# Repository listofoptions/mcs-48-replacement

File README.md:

# mcs-48-replacement
comaptible pinout controller for the mcs-48 microcontroller line using an AT90USB1286

features:
  - usb esd protection
  - power supply seperation and selection
  - reverse voltage protection (vcc/gnd swap)

  **__DO NOT ATTEMPT TO USE THIS CONTROLLER IN A MCS-48 PROGRAMMER__**
  **__THERE IS NO OVERVOLTAGE PROTECTION ON VDD, PROG, OR EA__**

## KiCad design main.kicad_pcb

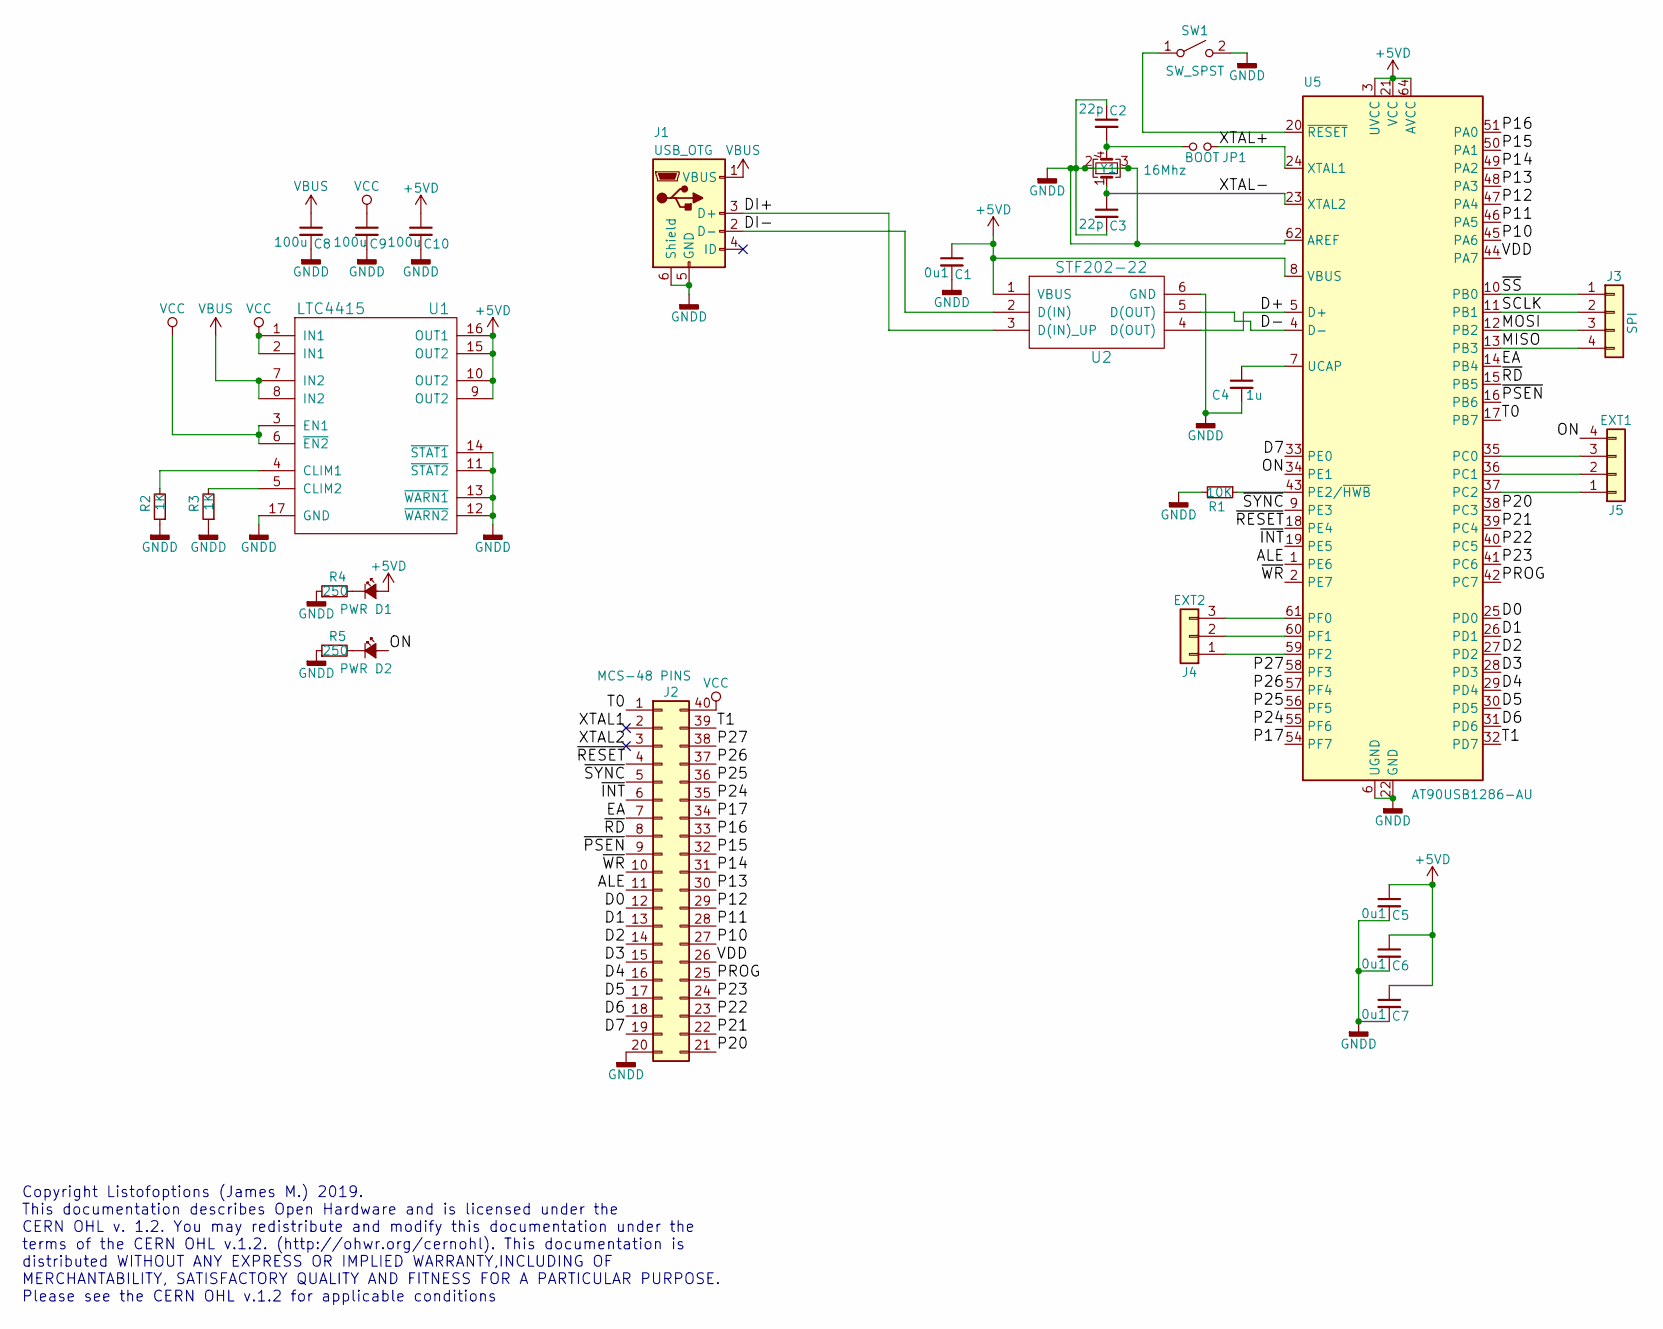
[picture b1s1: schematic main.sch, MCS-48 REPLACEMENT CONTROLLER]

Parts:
C1, C5, C6, C7: 0u1; C_0201
C2, C3: 22p; C_0201
C4: 1u; C_0201
C8, C9, C10: 100u; C_0805
D1, D2: PWR; LED_0402
J1: USB_OTG; USB_Micro-B_Molex-105017-0001
J2: MCS-48 PINS; DIP-40_W15.24mm
J3: SPI; Pin_Header_Straight_1x04_Pitch1.00mm
J4: EXT2; Pin_Header_Straight_1x03_Pitch1.00mm
J5: EXT1; Pin_Header_Straight_1x04_Pitch1.00mm
JP1: BOOT; R_0201_NoSilk
R1: 10K; R_0402
R2, R3: 1K; R_0402
R4, R5: 250; R_0402
SW1: SW_SPST; SW_SPST_B3U-3000P
U1: LTC4415; DFN-16-1EP_3x5mm_Pitch0.5mm
U2: STF202-22; TSOP-6_1.65x3.05mm_Pitch0.95mm
U5: AT90USB1286-AU; QFN-64-1EP_9x9mm_Pitch0.5mm
Y1: 16Mhz; Crystal_SMD_2016-4pin_2.0x1.6mm

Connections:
+5VD: C1.1, C5.1, C6.1, C7.1, C10.1, D1.2 (A), U1.9 (OUT2), U1.10 (OUT2), U1.15 (OUT2), U1.16 (OUT1), U2.1 (VBUS), U5.3 (UVCC), U5.8 (VBUS), U5.21 (VCC), U5.52 (VCC), U5.64 (AVCC)
/ALE: J2.11, U5.1 (PE6)
/D0: J2.12, U5.25 (PD0)
/D1: J2.13, U5.26 (PD1)
/D2: J2.14, U5.27 (PD2)
/D3: J2.15, U5.28 (PD3)
/D4: J2.16, U5.29 (PD4)
/D5: J2.17, U5.30 (PD5)
/D6: J2.18, U5.31 (PD6)
/D7: J2.19, U5.33 (PE0)
/D+: U2.4 (D(OUT)), U5.5 (D+)
/D-: U2.5 (D(OUT)), U5.4 (D-)
/DI+: J1.3 (D+), U2.3 (D(IN)_UP)
/DI-: J1.2 (D-), U2.2 (D(IN))
/EA: J2.7, U5.14 (PB4)
/MISO: J3.4, U5.13 (PB3)
/MOSI: J3.3, U5.12 (PB2)
/ON: D2.2 (A), J5.4, U5.34 (PE1)
/P10: J2.27, U5.45 (PA6)
/P11: J2.28, U5.46 (PA5)
/P12: J2.29, U5.47 (PA4)
/P13: J2.30, U5.48 (PA3)
/P14: J2.31, U5.49 (PA2)
/P15: J2.32, U5.50 (PA1)
/P16: J2.33, U5.51 (PA0)
/P17: J2.34, U5.54 (PF7)
/P20: J2.21, U5.38 (PC3)
/P21: J2.22, U5.39 (PC4)
/P22: J2.23, U5.40 (PC5)
/P23: J2.24, U5.41 (PC6)
/P24: J2.35, U5.55 (PF6)
/P25: J2.36, U5.56 (PF5)
/P26: J2.37, U5.57 (PF4)
/P27: J2.38, U5.58 (PF3)
/PROG: J2.25, U5.42 (PC7)
/SCLK: J3.2, U5.11 (PB1)
/T0: J2.1, U5.17 (PB7)
/T1: J2.39, U5.32 (PD7)
/VDD: J2.26, U5.44 (PA7)
/XTAL+: JP1.2, U5.24 (XTAL1)
/XTAL-: C3.1, U5.23 (XTAL2), Y1.1
/~INT: J2.6, U5.19 (PE5)
/~PSEN: J2.9, U5.16 (PB6)
/~RD: J2.8, U5.15 (PB5)
/~RESET: J2.4, U5.18 (PE4)
/~SS: J3.1, U5.10 (PB0)
/~SYNC: J2.5, U5.9 (PE3)
/~WR: J2.10, U5.2 (PE7)
GNDD: C1.2, C2.1, C3.2, C4.2, C5.2, C6.2, C7.2, C8.2, C9.2, C10.2, J1.5 (GND), J1.6 (Shield), J2.20, R1.2, R2.1, R3.1, R4.1, R5.1, SW1.2 (B), U1.11 (~STAT2), U1.12 (~WARN2), U1.13 (~WARN1), U1.14 (~STAT1), U1.17 (GND), U2.6 (GND), U5.6 (UGND), U5.22 (GND), U5.53 (GND), U5.62 (AREF), U5.63 (GND), U5.65, Y1.2, Y1.3
unnamed: C2.2, JP1.1, Y1.4
unnamed: C4.1, U5.7 (UCAP)
unnamed: D1.1 (K), R4.2
unnamed: D2.1 (K), R5.2
unnamed: J4.1, U5.59 (PF2)
unnamed: J4.2, U5.60 (PF1)
unnamed: J4.3, U5.61 (PF0)
unnamed: J5.1, U5.37 (PC2)
unnamed: J5.2, U5.36 (PC1)
unnamed: J5.3, U5.35 (PC0)
unnamed: R1.1, U5.43 (PE2/~HWB)
unnamed: R2.2, U1.4 (CLIM1)
unnamed: R3.2, U1.5 (CLIM2)
unnamed: SW1.1 (A), U5.20 (~RESET)
VBUS: C8.1, J1.1 (VBUS), U1.7 (IN2), U1.8 (IN2)
VCC: C9.1, J2.40, U1.1 (IN1), U1.2 (IN1), U1.3 (EN1), U1.6 (~EN2)

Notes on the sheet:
Copyright Listofoptions (James M.) 2019. This documentation describes Open Hardware and is licensed under the CERN OHL v. 1.2. You may redistribute and modify this documentation under the terms of the CERN OHL v.1.2. (http://ohwr.org/cernohl). This documentation is distributed WITHOUT ANY EXPRESS O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

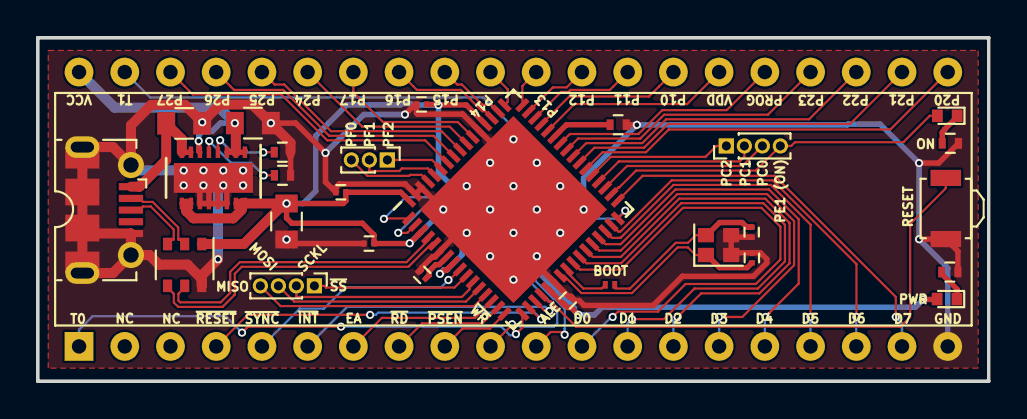
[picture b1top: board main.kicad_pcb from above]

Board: 2 copper layers, 52.8 x 19.1 mm, 28 parts (0 on the bottom side), 65 nets.

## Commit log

2019-04-01 intial commit, organization later
2019-04-01 cleaned up pcb, added status LEDs
2019-04-01 legal shenanigans
2019-04-01 Speeling
2019-04-01 organization
2019-04-03 improved groundplane, and used beefier supply caps
2019-04-03 bookeeping
2019-04-03 shenanigans and bootloader jumper on clock xtal-1 pin
2019-04-03 last minute 3d-shenanigans
